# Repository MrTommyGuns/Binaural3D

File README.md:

# Binaural3D
TFG: "Diseño de un Micrófono Biaural para Captación de Sonido Realista"

## Resumen

Diseño e implementación de un micrófono
biaural para la captación de sonidos realistas. Consta de electrónica analógica y un diseño
tridimensional realizado mediante impresión 3D FDM.

Para el diseño 3D se partió de recursos libres de derechos para la modificación, a partir
de los cuales se llevó a cabo una total remodelación para garantizar un sistema modular
con el que realizar diferentes grabaciones dependiendo de las suposiciones requeridas. Por
consiguiente, mediante el intercambio de piezas de una misma unidad se puede variar la
ubicación de la cápsula microfónica en el oído emulado, el tamaño y forma de las orejas,
siendo estos parámetros fundamentales para generar una sensación psicoacústica correcta
para cada individuo. De este modo, se consigue un sistema muy versátil.

El circuito electrónico consiste en un preamplificador de varias etapas, donde se amplifica
la señal recogida por las cápsulas microfónicas situadas en el diseño 3D que recrea
una cabeza, simulando la captación de sonidos del oído humano. Para la implementación
de este circuito electrónico, se han llevado a cabo diferentes etapas. En primer lugar se
realizó el estudio de las cápsulas microfónicas de tipo electret, para su posterior acondicionamiento
y amplificación. Posteriormente mediante simulación se realizó un primer
circuito preamplificador simple y el primer prototipo mediante protoboard. Una vez alcanzados
unos resultados satisfactorios se inició el proceso de diseño de la PCB, incrementando
la complejidad del circuito mediante la implementación de nuevas configuraciones
de amplificación y la adhesión de un sistema de balanceo de la señal. Se realizaron una serie
de medidas eléctricas para la verificación del correcto funcionamiento y se corrigieron
los errores encontrados. Finalmente, se realizó el circuito final junto a la PCB definitiva y
se realizaron test de funcionamiento y caracterización.

## Vídeo

https://youtu.be/iz7Ld4p7Zro

https://youtu.be/ZWAR-ZuT80Q

## Autor

### Tomás Criado Galache

## Palabras clave

Micrófono Biaural; Preamplificador; Impresión 3D

Key words: Binaural Microphone; Preamplifier; 3D Print

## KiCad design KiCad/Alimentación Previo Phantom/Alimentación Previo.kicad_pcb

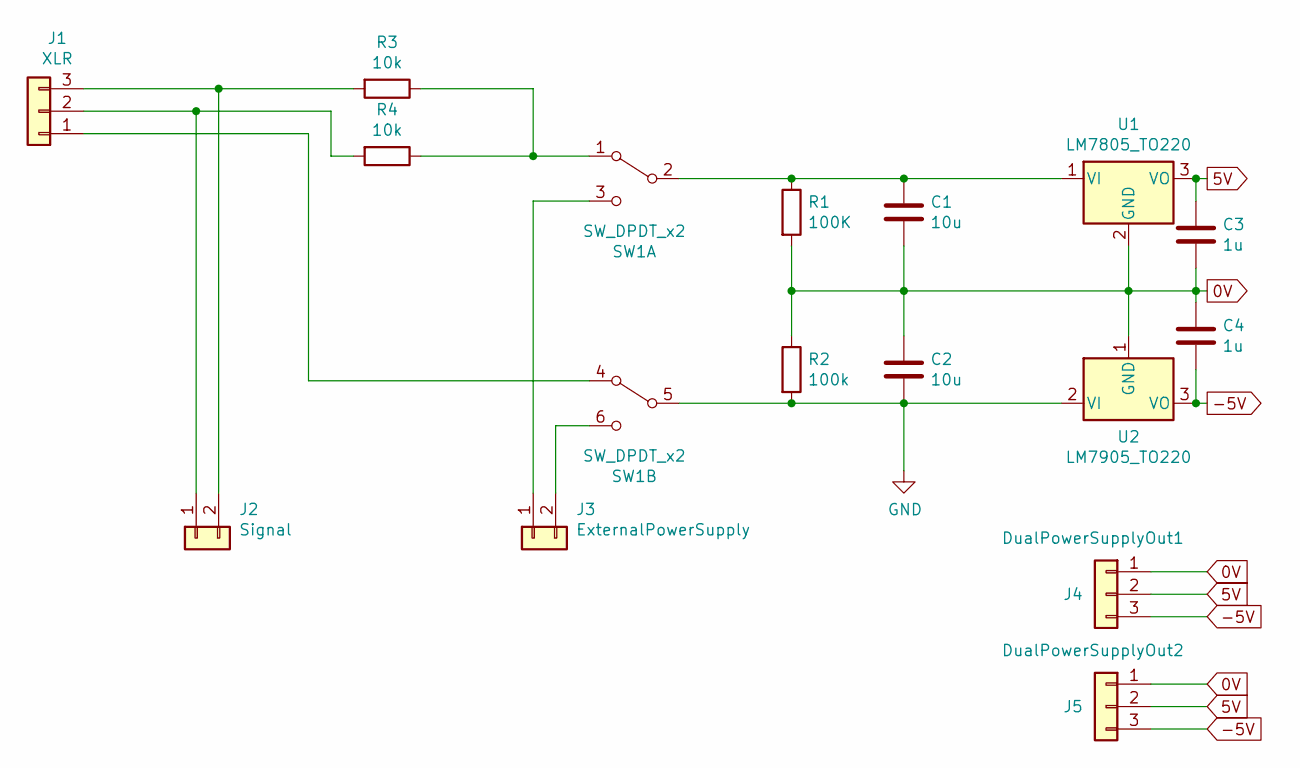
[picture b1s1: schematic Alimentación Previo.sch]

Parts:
C1, C2: 10u; CP_Radial_D8.0mm_P5.00mm
C3, C4: 1u; CP_Radial_D8.0mm_P5.00mm
J1: XLR; SolderWire-0.5sqmm_1x03_P4.8mm_D0.9mm_OD2.3mm
J2: Signal; SolderWire-0.5sqmm_1x02_P4.8mm_D0.9mm_OD2.3mm
J3: ExternalPowerSupply; SolderWire-0.5sqmm_1x02_P4.8mm_D0.9mm_OD2.3mm
J4: DualPowerSupplyOut1; SolderWire-0.5sqmm_1x03_P4.8mm_D0.9mm_OD2.3mm
J5: DualPowerSupplyOut2; SolderWire-0.5sqmm_1x03_P4.8mm_D0.9mm_OD2.3mm
R1: 100K; R_Axial_DIN0207_L6.3mm_D2.5mm_P10.16mm_Horizontal
R2: 100k; R_Axial_DIN0207_L6.3mm_D2.5mm_P10.16mm_Horizontal
R3, R4: 10k; R_Axial_DIN0207_L6.3mm_D2.5mm_P10.16mm_Horizontal
SW1: SW_DPDT_x2; SW_E-Switch_EG1271_DPDT
U1: LM7805_TO220; TO-220-3_Vertical
U2: LM7905_TO220; TO-220-3_Vertical

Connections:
0V: C1.2, C2.1, C3.2, C4.1, J4.1, J5.1, R1.2, R2.1, U1.2 (GND), U2.1 (GND)
5V: C3.1, J4.2, J5.2, U1.3 (VO)
-5V: C4.2, J4.3, J5.3, U2.3 (VO)
GND: C2.2, R2.2, SW1.5 (B), U2.2 (VI)
unnamed: C1.1, R1.1, SW1.2 (B), U1.1 (VI)
unnamed: J1.1, SW1.4 (A)
unnamed: J1.2, J2.1, R4.2
unnamed: J1.3, J2.2, R3.2
unnamed: J3.1, SW1.3 (C)
unnamed: J3.2, SW1.6 (C)
unnamed: R3.1, R4.1, SW1.1 (A)

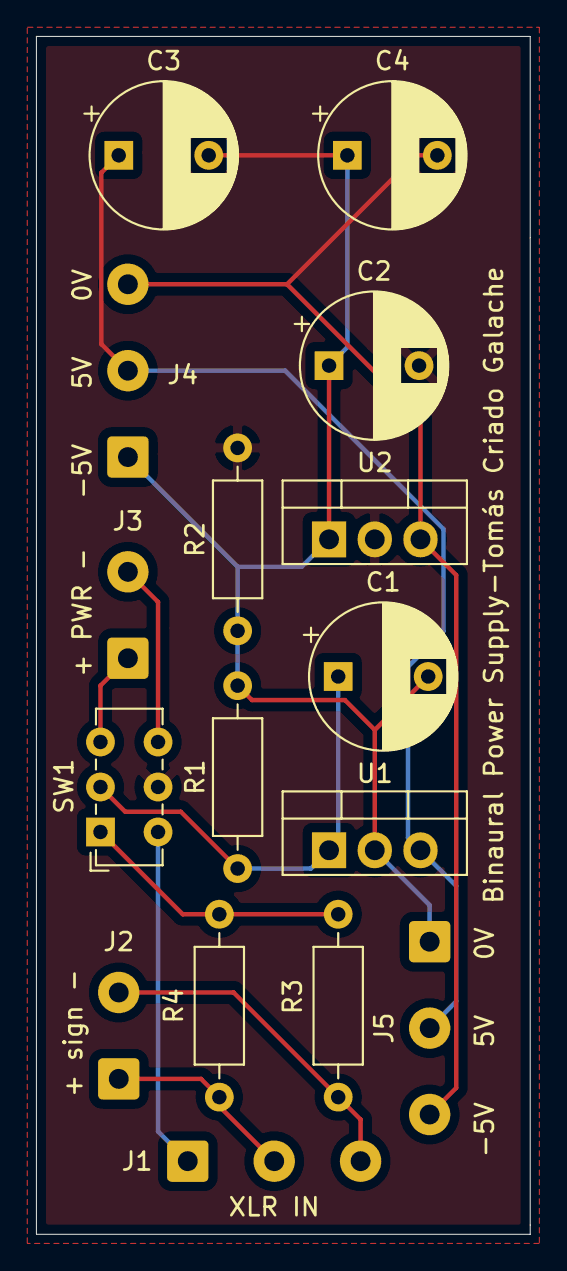
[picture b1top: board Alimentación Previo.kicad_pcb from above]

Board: 2 copper layers, 27.4 x 66.5 mm, 16 parts (0 on the bottom side), 11 nets.

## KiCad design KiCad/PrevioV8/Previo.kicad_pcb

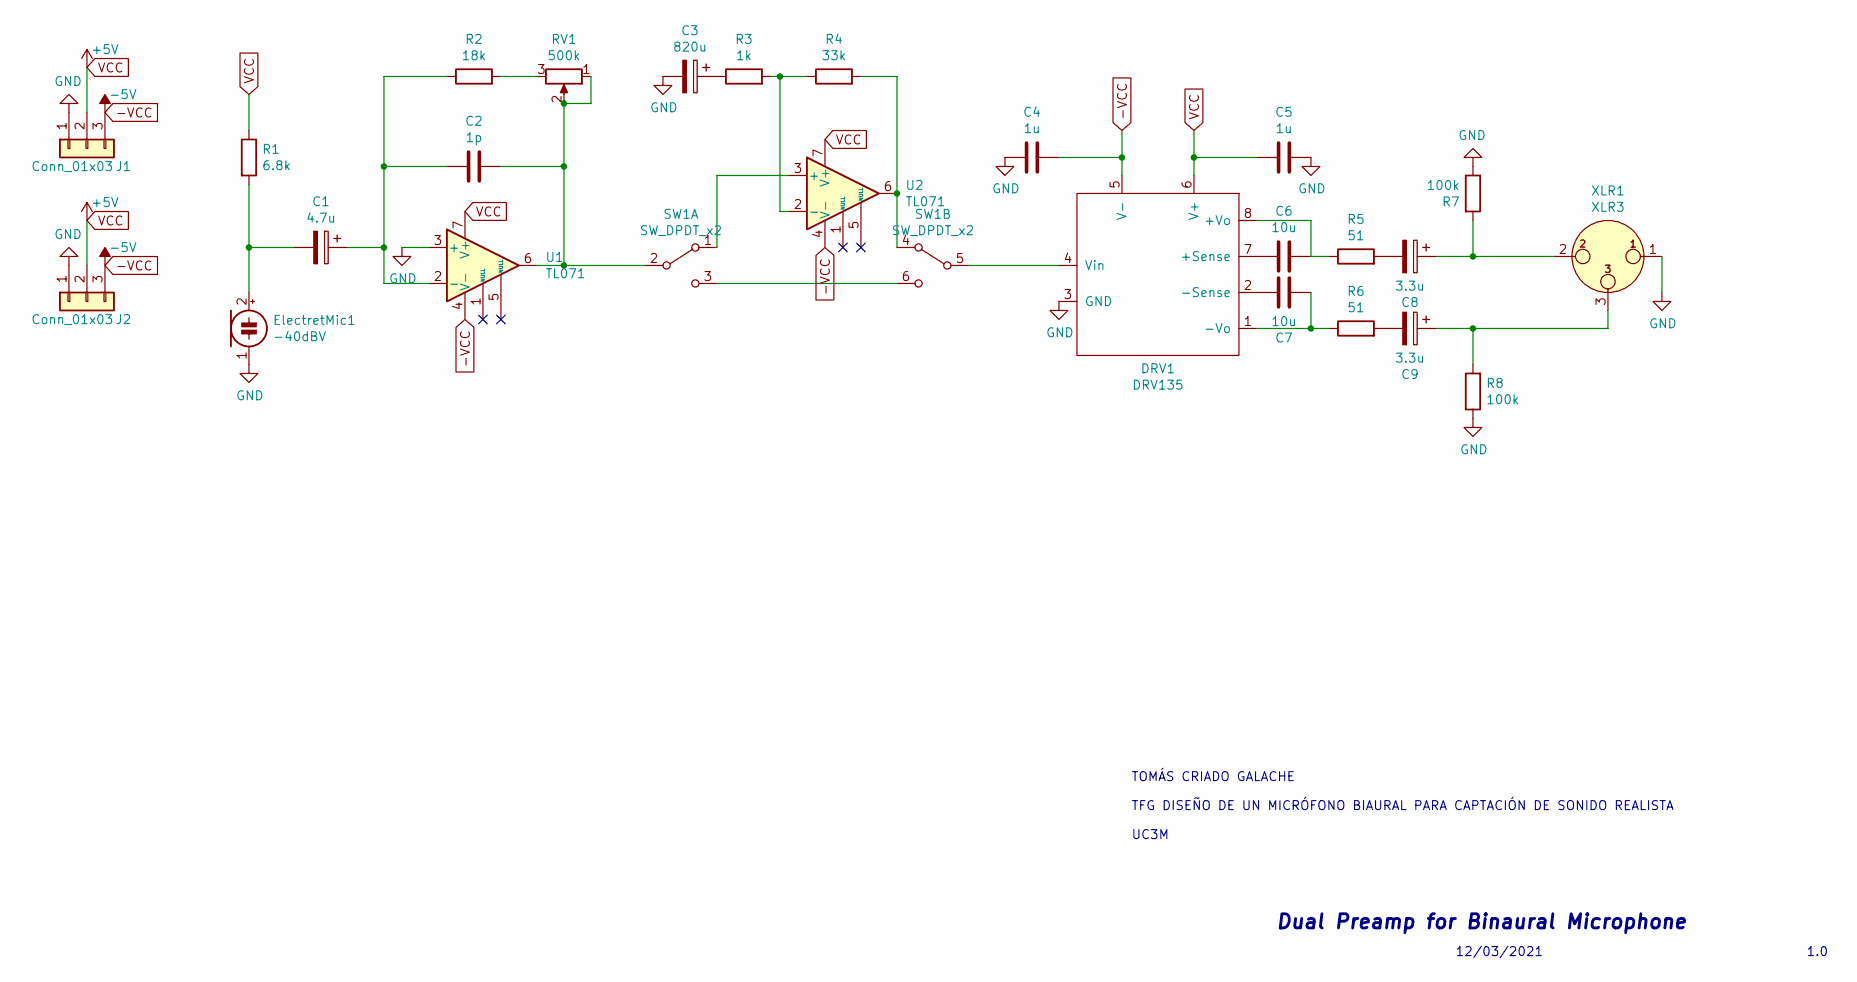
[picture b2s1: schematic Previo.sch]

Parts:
C1: 4.7u; CP_Radial_D8.0mm_P5.00mm
C2: 1p; C_Rect_L7.0mm_W4.5mm_P5.00mm
C3: 820u; CP_Radial_D8.0mm_P5.00mm
C4, C5: 1u; C_Rect_L7.0mm_W4.5mm_P5.00mm
C6, C7: 10u; C_Rect_L7.0mm_W4.5mm_P5.00mm
C8, C9: 3.3u; CP_Radial_D8.0mm_P5.00mm
DRV1: DRV135; DIP-8_W7.62mm_LongPads
ElectretMic1: -40dBV; PhoenixContact_MSTBVA_2,5_2-G_1x02_P5.00mm_Vertical
J1, J2: Conn_01x03; SolderWire-0.5sqmm_1x03_P4.8mm_D0.9mm_OD2.3mm
R1: 6.8k; R_Axial_DIN0207_L6.3mm_D2.5mm_P10.16mm_Horizontal
R2: 18k; R_Axial_DIN0207_L6.3mm_D2.5mm_P10.16mm_Horizontal
R3: 1k; R_Axial_DIN0207_L6.3mm_D2.5mm_P10.16mm_Horizontal
R4: 33k; R_Axial_DIN0207_L6.3mm_D2.5mm_P10.16mm_Horizontal
R5, R6: 51; R_Axial_DIN0207_L6.3mm_D2.5mm_P10.16mm_Horizontal
R7, R8: 100k; R_Axial_DIN0207_L6.3mm_D2.5mm_P10.16mm_Horizontal
RV1: 500k; SolderWire-0.5sqmm_1x03_P4.8mm_D0.9mm_OD2.3mm
SW1: SW_DPDT_x2; SolderWire-0.5sqmm_1x06_P4.8mm_D0.9mm_OD2.3mm
U1, U2: TL071; DIP-8_W7.62mm_LongPads
XLR1: XLR3; SolderWire-0.5sqmm_1x03_P4.8mm_D0.9mm_OD2.3mm

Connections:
-VCC: C4.1, DRV1.5 (V-), J1.3, J2.3, U1.4 (V-), U2.4 (V-)
GND: C3.2, C4.2, C5.1, DRV1.3 (GND), ElectretMic1.1 (-), J1.1, J2.1, R7.1, R8.1, U1.3 (+), XLR1.1
unnamed: C1.1, C2.2, R2.1, U1.2 (-)
unnamed: C1.2, ElectretMic1.2 (+), R1.2
unnamed: C2.1, RV1.1, RV1.2, SW1.2 (B), U1.6
unnamed: C3.1, R3.1
unnamed: C6.1, DRV1.8 (+Vo), R5.1
unnamed: C6.2, DRV1.7 (+Sense)
unnamed: C7.1, DRV1.2 (-Sense)
unnamed: C7.2, DRV1.1 (-Vo), R6.1
unnamed: C8.1, R7.2, XLR1.2
unnamed: C8.2, R5.2
unnamed: C9.1, R8.2, XLR1.3
unnamed: C9.2, R6.2
unnamed: DRV1.4 (Vin), SW1.5 (B)
unnamed: R2.2, RV1.3
unnamed: R3.2, R4.1, U2.2 (-)
unnamed: R4.2, SW1.4 (A), U2.6
unnamed: SW1.1 (A), U2.3 (+)
unnamed: SW1.3 (C), SW1.6 (C)
VCC: C5.2, DRV1.6 (V+), J1.2, J2.2, R1.1, U1.7 (V+), U2.7 (V+)

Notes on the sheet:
12/03/2021
1.0
Dual Preamp for Binaural Microphone
TOMÁS CRIADO GALACHE TFG DISEÑO DE UN MICRÓFONO BIAURAL PARA CAPTACIÓN DE SONIDO REALISTA UC3M

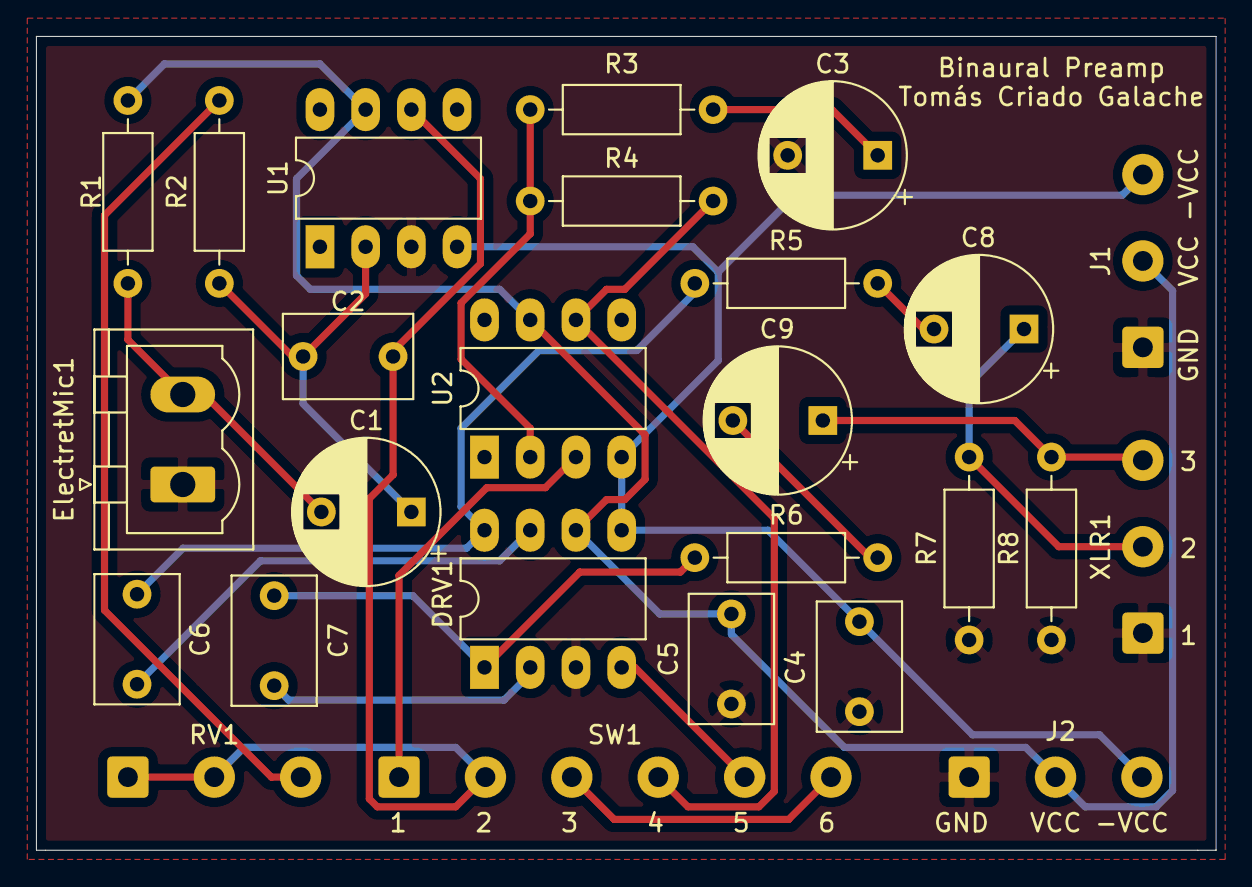
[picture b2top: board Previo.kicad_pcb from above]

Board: 2 copper layers, 65.5 x 45.2 mm, 26 parts (0 on the bottom side), 21 nets.

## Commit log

2021-08-23 Memoria TFG
2021-08-23 Simulaciones LTspice
2021-08-23 Archivos KiCad
2021-08-23 Diseños 3D
2021-08-23 Resumen
2021-08-23 Fotos
